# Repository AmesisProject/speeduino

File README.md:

AmesisProject Version Mod for TrottleBody VAG
<div align="center">

You can see Rev1.0 here https://www.instagram.com/p/CWWm2S4oEU1/
 
 You can follow my project here https://www.youtube.com/watch?v=GH1-DV4onDg&list=PLcTQwPiio2_Nbu8X9_lO5LS0OjIScwXXp&index=1&t=3s
 
<div align="center">

##### A low cost, DIY friendly Engine Management System (ECU) based on the Arduino framework
</div>

## Speeduino
The Speeduino project is a flexible, fully featured Engine Management Systems (EMS aka ECU) based on the low cost and open source Arduino platform. It provides the hardware, firmware and software components that make up an engine management system, all provided under open licenses. With over 1000 installations, Speeduino has matured into a product that meets the needs of the hobbyist and enthusiast community without driving prices to the levels of traditional aftermarket ECUs.

## Documentation
The Speeduino online manual can be found at: https://wiki.speeduino.com

## Where to Buy
[Pre-made Speeduino units/boards are available from a number of official resellers](https://speeduino.com/home/where-to-buy)

These resellers all contribute a portion of sales back to the project to allow for continued development to take place and we encourage sales through them whenever possible. 
 
Of course, being open source, you are free to use the design files provided here to create your own hardware! 

## Support
In addition the manual referenced above, Speeduino has a large and very vibrant community of people to help out with your setup or any questions you might add. 

* [Speeduino Forum](https://speeduino.com/forum) 
* [Slack](https://speeduino.com/home/community/slack)
* [Facebook](https://www.facebook.com/groups/191918764521976/)

## Contributors

This project exists thanks to all the people who contribute, both in terms of code and testing provided. If you'd like to get involved, please have a read through [Contributing](contributing.md) and then jump on Slack to discuss things further

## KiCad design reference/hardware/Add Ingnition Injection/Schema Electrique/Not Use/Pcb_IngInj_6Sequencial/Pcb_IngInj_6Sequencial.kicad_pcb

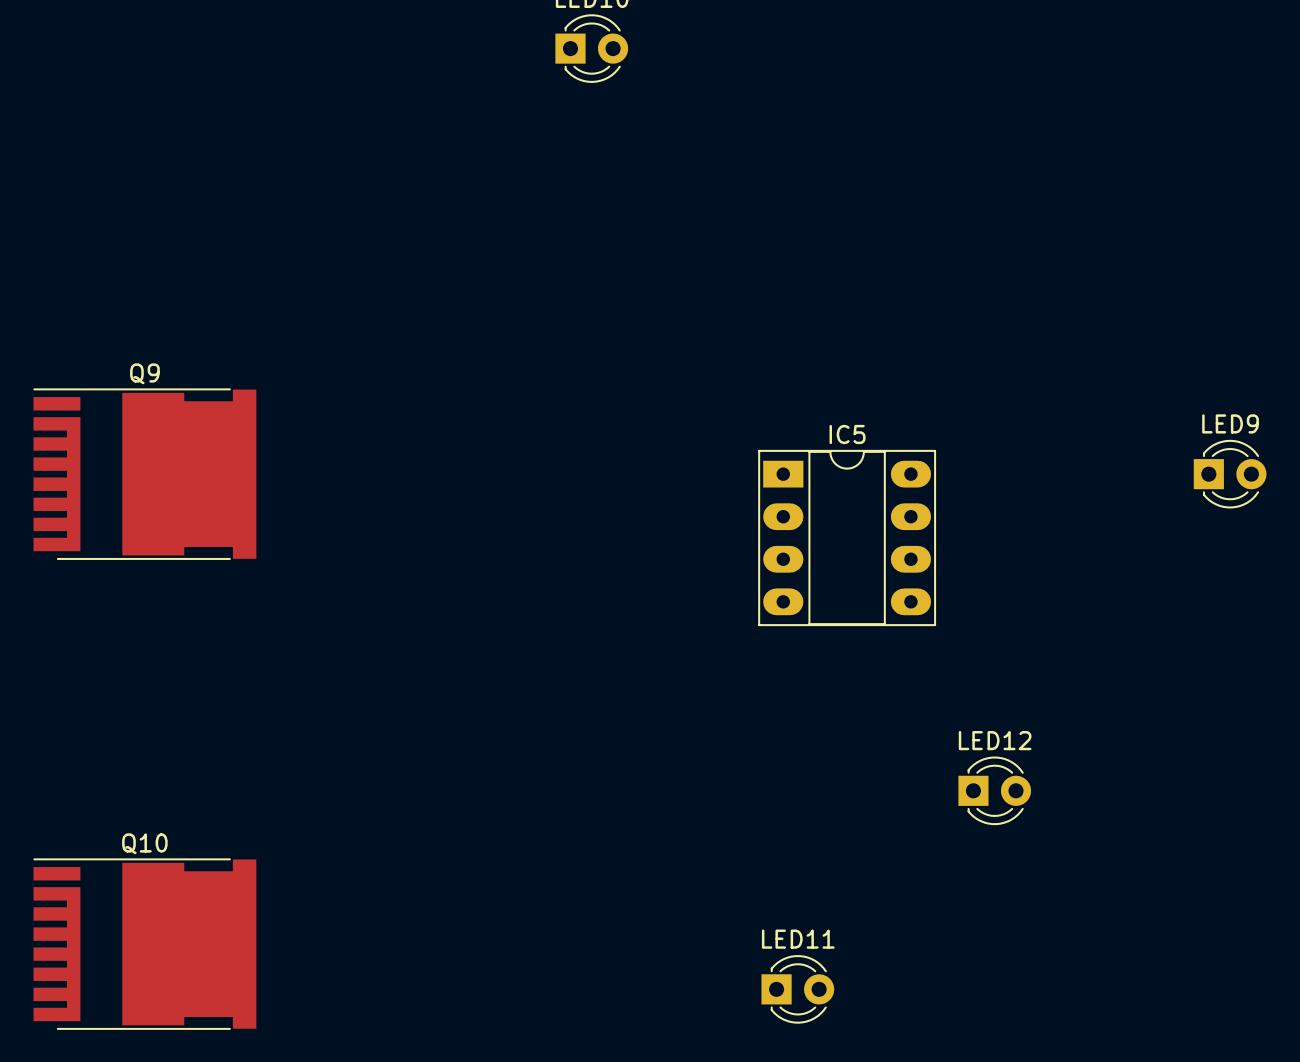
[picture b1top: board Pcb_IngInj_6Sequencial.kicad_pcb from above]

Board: 2 copper layers, 7 parts (0 on the bottom side), 2 nets, no tracks yet.

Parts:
IC5: TC4424EPA; DIP-8_W7.62mm_Socket_LongPads
LED9, LED10, LED11, LED12: Red; LED_D3.0mm
Q9, Q10: STP62NS04Z; Infineon_PG-HSOF-8-1

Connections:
GNDREF: IC5.3 (GND), LED9.1 (K), LED10.1 (K), Q9.2 (S), Q10.2 (S)
unnamed: IC5.1 (NC), IC5.8 (NC)

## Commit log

2021-10-31 update Speeduino teste 1.ini
    Mise a jour du ini car a 255 il affichait 99% et a 254 il affiche bien 100%
2021-11-03 globals.h
    Mise a jour d'un nom variable. legère correction
2021-11-03 Revert "globals.h"
    This reverts commit edbf9b6ceaec971258b732adee2a118b0293d0ee.
2021-11-03 Revert "Revert "globals.h""
    This reverts commit b0c043fe9b01d19c895cf7b859c147908a424ca5.
2021-11-03 Update speeduino test 1.ini
    Voir poste presedent, mise a jour du fichier ini pour les jauges ADC et % du ThrottleBody
2021-11-03 ThrottleBody Sensor Ok
    Mise a jour des fichiers, pour le calibrage du capteur de position papillon et les jauge ADC et % sont fonctionnel
    Ne reste plus qu'a faire un test d'écriture (digital right) pour par la suit inclure le code du papillon motorisé
    Updated files, for the calibration of the throttle position sensor and the ADC and% gauges are functional
    All that remains is to do a writing test (digital right) to subsequently include the motorized throttle code
2021-11-08 Commande H Bridge Motor 1 & 2 ok (2021/11/08)
    Création du code pour le digitalWrite pour commander les bornes in1 et in2 du module H-Bridge. Possiblilité de choisir le pin de sortie dans tunerStudio. Non testé sur le module réel mais sur les led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
    A faire, le code est dans sensor.ino il faut creer les fichiers dédiés a l'option ThrottleBody. ino & .h
    Tester le module L298N H-Bridge en reél.
    Activer le PWM pin ENA pour la variation de vitesse pour les futurs PID
    Creation of the code for the digitalWrite to control the in1 and in2 terminals of the H-Bridge module. Possibility to choose the output pin in tunerStudio. Not tested on the real module but on the le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
    To do this, the code is
2021-11-08 Création Fichier ThrottleBody
    Création des fichier .H et .INO
2021-11-09 Update sensors.ino
    adaptation
2021-11-13 Creat .ino & .h ThrottleBody
    Bascule du code dans des fichiers isolé
2021-11-26 PPSTotal
    teste de la variable PPS Total qui fait la moyenne de PPS1 + PPS2.
    Mise en place aussi d'une plage de tolerence de 10% de difference entre les deux pedales. A tester
2021-12-19 Update ThrottleBody.ino
    teste d'un nouveau code simplifier (non tester un réél)
2021-12-19 Create Dropbear _ Manuel Speeduino vf.pdf
    save garde de la documentation en français de la board dropbear
2021-12-22 Save
    Création d'un dossier de sauvegade pour les codes fonctionnel ou en cour. ajout de impre ecran de tunerStudio nouvel fenetre creer
2021-12-22 Update README.md
    add pictur en videos lien
2021-12-30 Modul Ingition Injection 6 Cylindre
    Création d'un module pour du sequenciel en 6 cylindres adaptable au speeduino 0.4.3
    -Creation du schema sur kicad
2022-01-01 Plan Kicad
    Mise a jour du plan kicad
2022-01-01 Kicad ing inj
    Mise a jour du plan kicad
2022-01-02 Création Fritzing
    Test de cration du projet sous Fritzing 6 et 8 cylindre. mais attenttion ces versions ont baucoup d'erreur
2022-01-02 Update ThrottleBody.h
    MAJ
2022-01-04 Create Ingition Injector 5-6 Sequancial Modul Rev.0.1.fzz
    Creation du fiechier Rev0.1 du modul full sequantial 5-6 cylindre pour speeduino.
2022-01-04 PCB Ok Rev0.1
    Finition du fritzing 5-6 et commande passer pour le Rev0.1
2022-01-09 kicad
    ouverture du fichier Rien ras
2022-01-09 Deplassement de fichier
    Création d'un nouveau Git
2022-01-19 autosave
    RAS
2022-04-01 Update ThrottleBody.ino
    ??
2022-04-01 platformeiot.ini
    supr pltate forme iot
2022-04-01 Update idle.ino
    etude du fichier idle pour le throttle body, pmis en place de commantaire dans le fichier
2022-04-01 Update ThrottleBody.ino
    TO Do liste
2022-04-12 ajout de page ds global.h
    peut etre l'audroit pour rajouter des page
2022-05-28 documentation doxygen
    ouvrir le fichier index.html pour consulter
2023-05-04 Mise a jour du FW
2023-05-07 Ajout des carte MegaSpeedoMini et MegaSpeedo 6zyl THT au ini et pinout
2023-07-09 Create Acelerador_V04_03.ino
    pid test

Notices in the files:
README.md:
License: GPLv3
